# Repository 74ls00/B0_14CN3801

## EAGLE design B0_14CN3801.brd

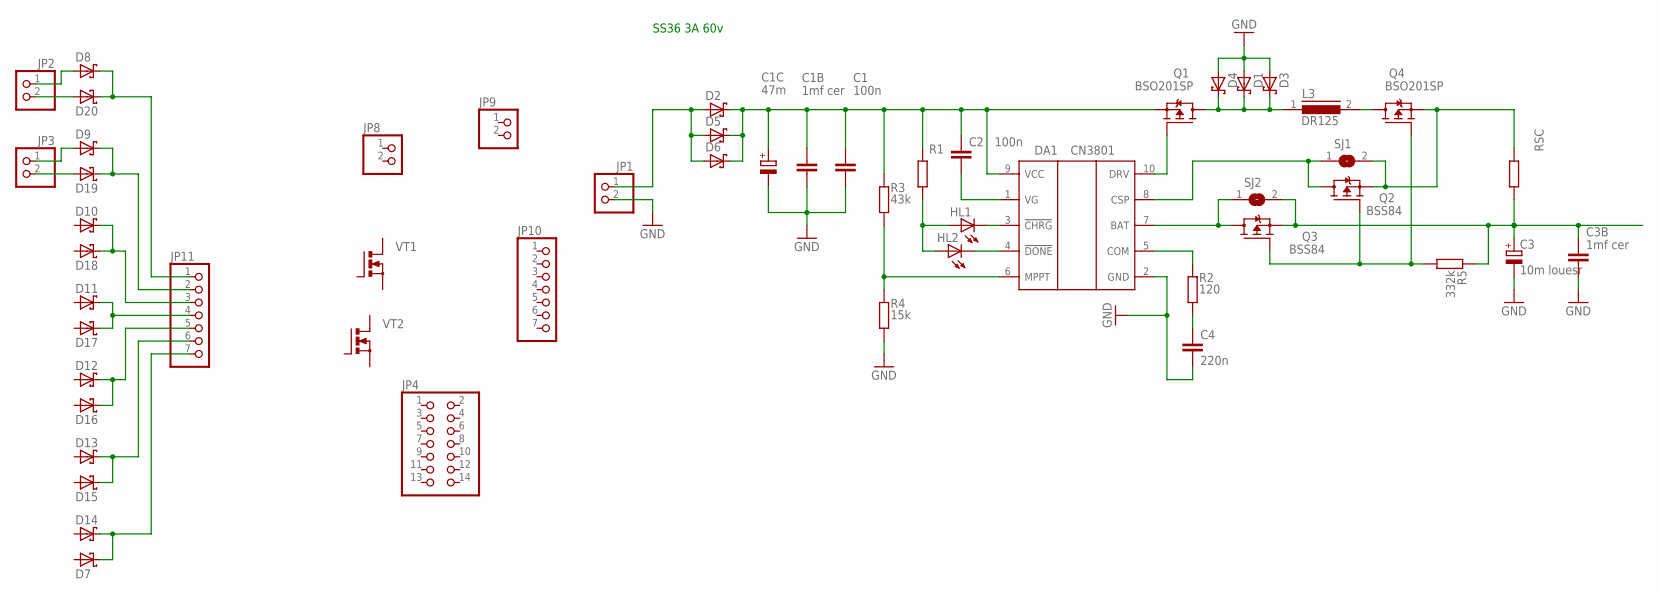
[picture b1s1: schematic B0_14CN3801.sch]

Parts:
C1, C2: 100n; C0805
C1B, C3B: 1mf cer; C0805
C1C: 47m; E2,5-6
C3: 10m louesr; E2,5-6
C4: 220n; C0805
D1, D2, D3, D4, D5, D6, D7, D8, D9, D10, D11, D12, D13, D14, D15, D16, D17, D18, D19, D20: SCHOTTKY-DIODESMC; SMC
DA1: CN3801; SSOP10
HL1, HL2: LEDCHIPLED_0603; CHIPLED_0603
JP1, JP2, JP3, JP8, JP9: PINHD-1X2/2; 1X02
JP4: PINHD-2X7; 2X07
JP10, JP11: PINHD-1X7; 1X07
L3: DR125
Q1, Q4: BSO201SP; SO-8
Q2, Q3: BSS84; SC75_INFINEON
R1: R-EU_R0805; R0805
R2: 120; R0805
R3: 43k; R0805
R4: 15k; R0805
R5: 332k; R0805
RSC: R-EU_R0805; R0805
SJ1, SJ2: SJ
VT1, VT2: MOSFET-N_TO220_H; TO220BH

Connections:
BAT: DA1.7 (BAT), Q3.2 (D), SJ2.1
COM: DA1.5 (COM), R2.2
CSP: DA1.8 (CSP), Q2.2 (D), SJ1.1
GND: C1.2, C1B.2, C1C.-, C3.-, C3B.2, C4.2, D1.A, D3.A, D4.A, DA1.2 (GND), JP1.2, R4.1
unnamed: C1.1, C1B.1, C1C.+, C2.1, D2.C, D5.C, D6.C, DA1.9 (VCC), Q1.1 (S), Q1.2 (S), Q1.3 (S), R1.2, R3.2
unnamed: C2.2, DA1.1 (VG)
unnamed: DA1.6 (MPPT), R3.1, R4.2
unnamed: D2.A, D5.A, D6.A, JP1.1
unnamed: HL1.A, HL2.A, R1.1
unnamed: DA1.3 (!CHRG), HL1.C
unnamed: DA1.4 (!DONE), HL2.C
unnamed: C4.1, R2.1
unnamed: DA1.10 (DRV), Q1.4 (G)
unnamed: D7.C, D14.C, JP11.7
unnamed: L3.2, Q4.5 (D), Q4.6 (D), Q4.7 (D), Q4.8 (D)
unnamed: Q2.1 (G), Q3.1 (G), Q4.4 (G), R5.1
unnamed: D1.C, D3.C, D4.C, L3.1, Q1.5 (D), Q1.6 (D), Q1.7 (D), Q1.8 (D)
unnamed: Q2.3 (S), Q4.1 (S), Q4.2 (S), Q4.3 (S), RSC.2, SJ1.2
unnamed: C3.+, C3B.1, Q3.3 (S), R5.2, RSC.1, SJ2.2
unnamed: D13.C, D15.C, JP11.6
unnamed: D12.C, D16.C, JP11.5
unnamed: D11.C, D17.C, JP11.4
unnamed: D10.C, D18.C, JP11.3
unnamed: D9.C, D19.C, JP11.2
unnamed: D8.C, D20.C, JP11.1
unnamed: D19.A, JP3.2
unnamed: D9.A, JP3.1
unnamed: D8.A, JP2.1
unnamed: D20.A, JP2.2

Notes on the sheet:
SS36 3A 60v

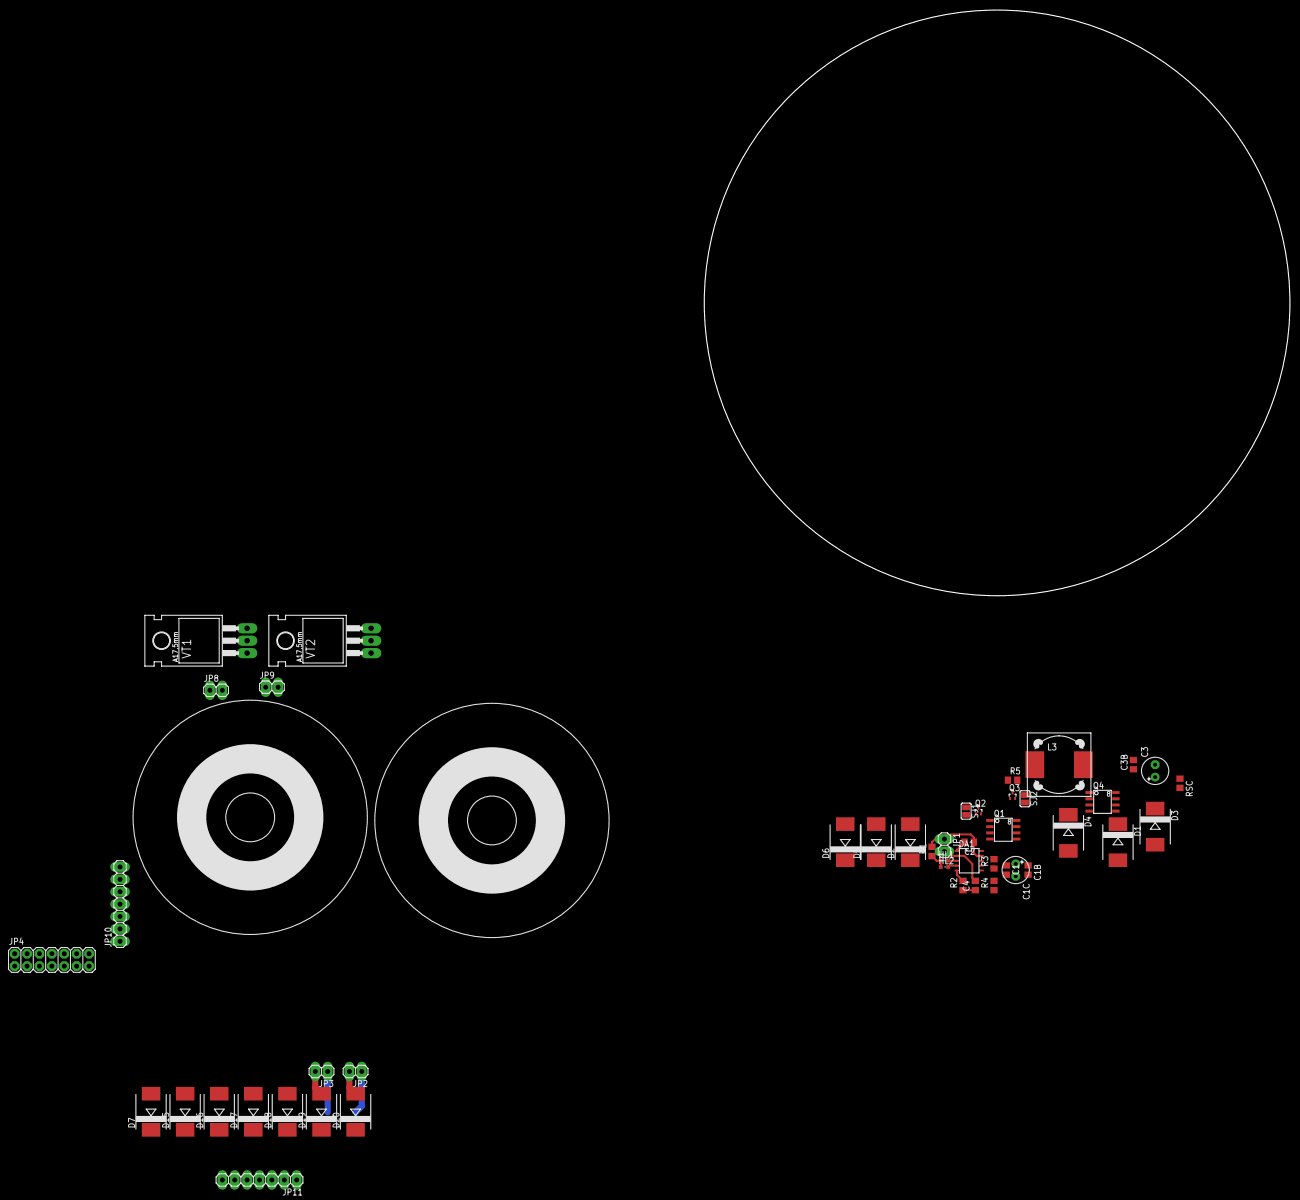
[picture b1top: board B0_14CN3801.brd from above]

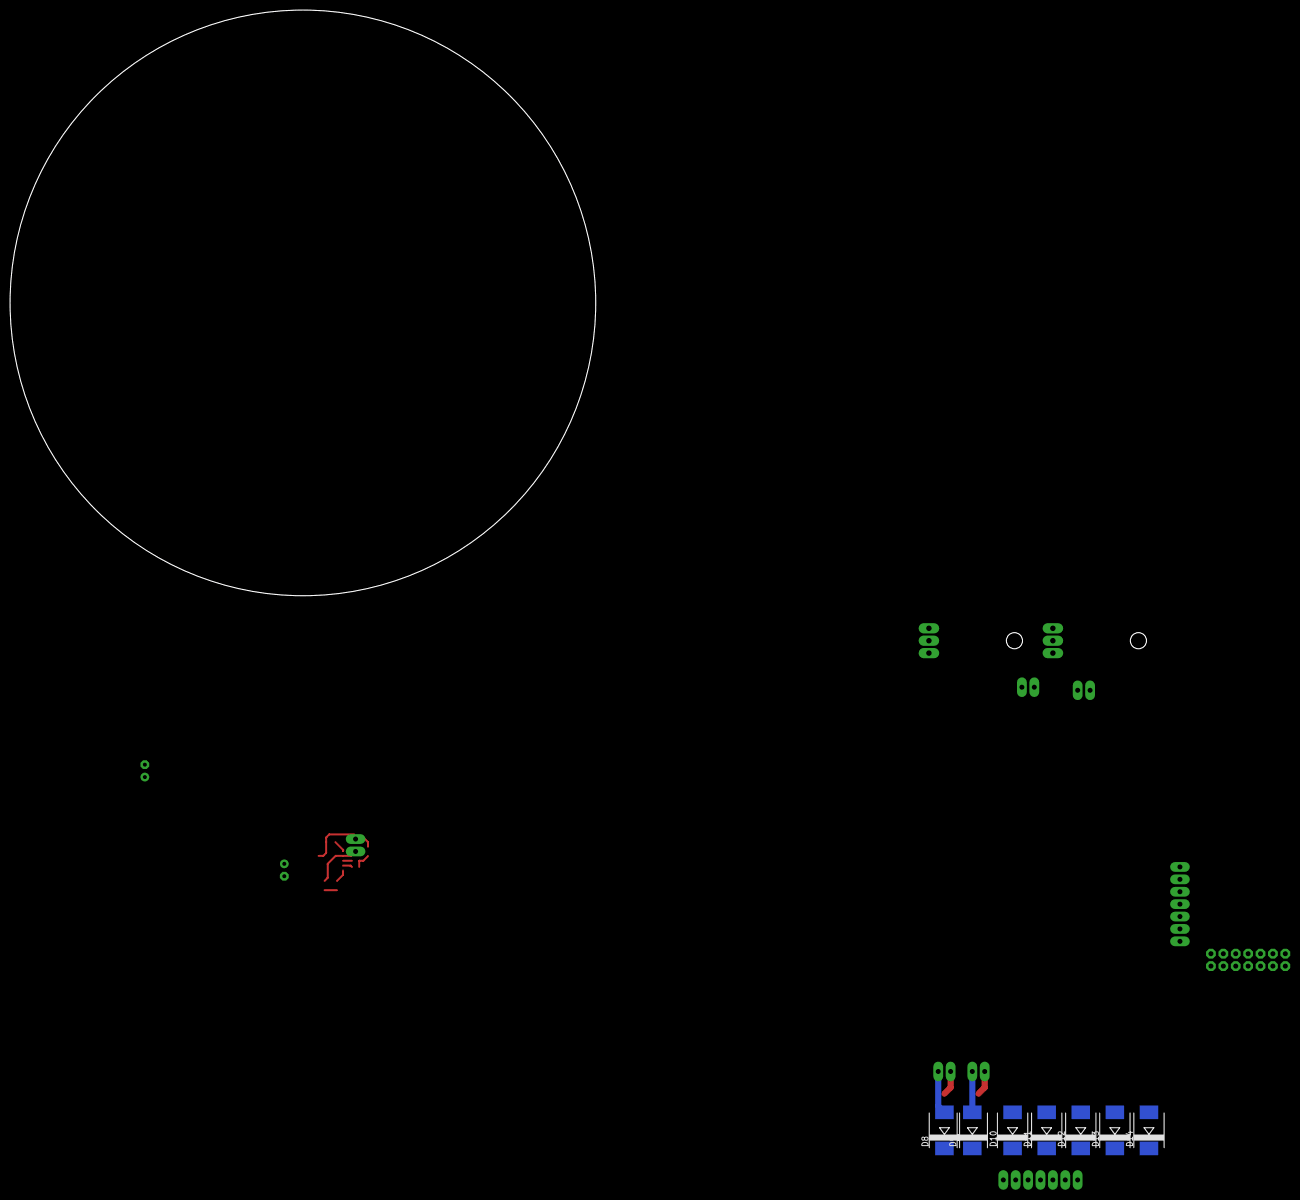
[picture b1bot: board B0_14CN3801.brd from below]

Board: 2 copper layers, 120.0 x 120.0 mm, 56 parts (7 on the bottom side), 29 nets.

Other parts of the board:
U$1: PCB1
U$2, U$3: T48K30
